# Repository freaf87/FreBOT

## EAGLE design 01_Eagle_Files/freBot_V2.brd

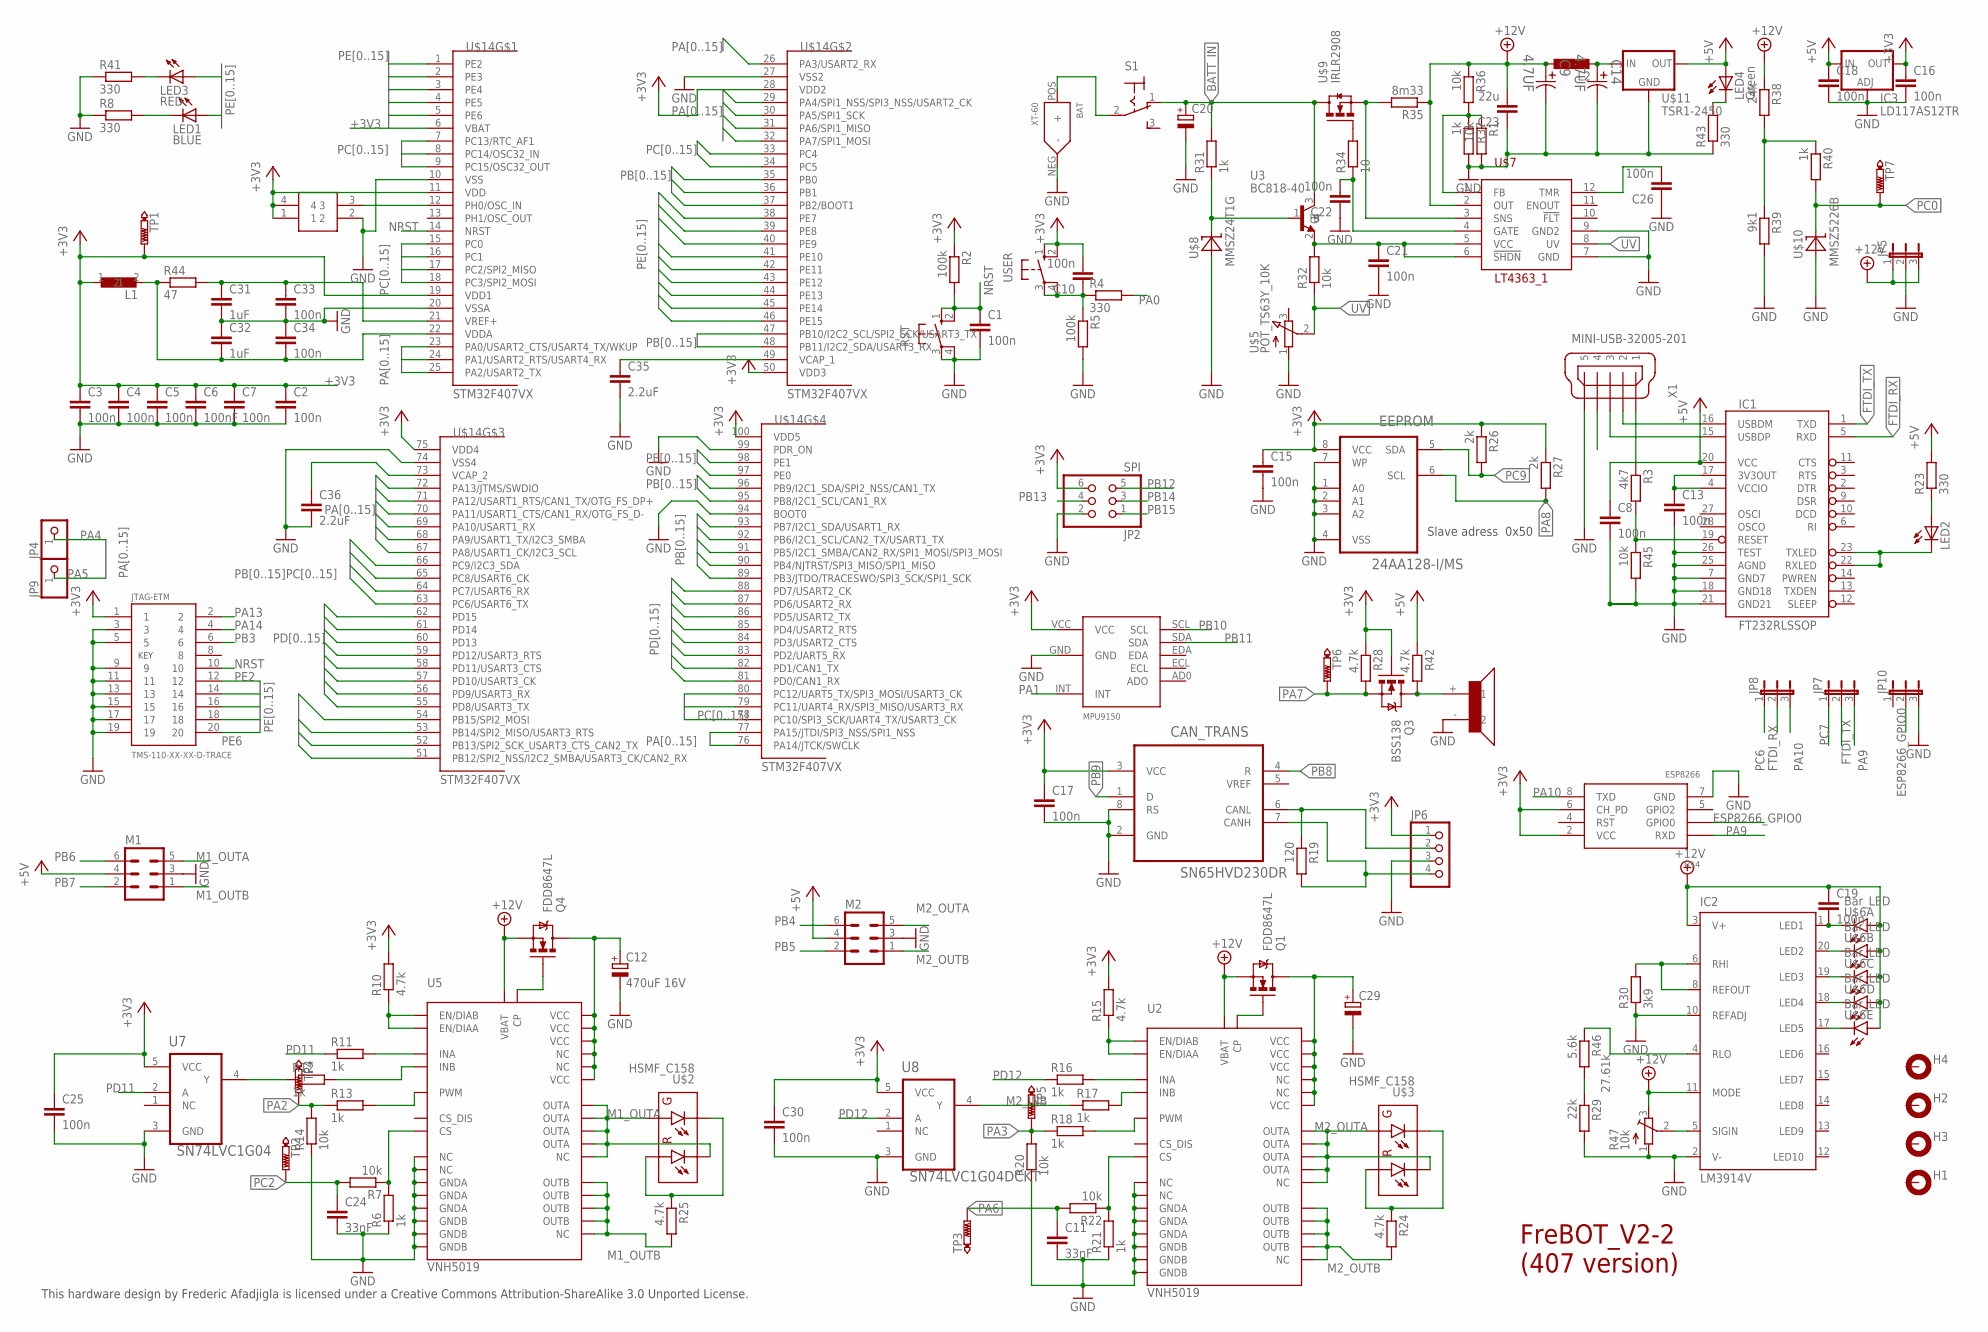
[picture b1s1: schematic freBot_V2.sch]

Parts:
BAT: XT-60
C1, C2, C3, C4, C5, C7, C8, C10, C13, C15, C16, C17, C18, C19, C21, C33, C34: 100n; C0603
C6: 100nF; C0603
C9, C14: 4.7UF; CAPAE330X560N
C11, C24: 33nF; C0805
C12: 470uF 16V; 175TMP-0808
C20: CPOL-EU153CLV-0505; 153CLV-0505
C22, C26: 100n; C0805
C23: 22u; C0805
C25, C30: 100n; C0603K
C29: CPOL-EU175TMP-0808; 175TMP-0808
C31, C32: 1uF; C0603
C35, C36: 2.2uF; C0805
CAN_TRANS: SN65HVD230DR; SOIC127P600X175-8N
EEPROM: 24AA128-I/MS; SOP65P490X110-8N
H1, H2, H3, H4: MOUNT-PAD-ROUND3.0; 3,0-PAD
IC1: FT232RLSSOP; SSOP28DB
IC2: LM3914V; PLCC20S
IC3: LD117AS12TR; SOT223
JP2: SPI; 2X03
JP4, JP9: PINHD-1X1; 1X01
JP5, JP7, JP8, JP10: JP2E; JP2
JP6: PINHD-1X4; 1X04
JTAG-ETM: TMS-110-XX-XX-D-TRACE
L1: FERRITPERLE_0805
L2: L-EUWE-TPC; POWER-CHOKE_WE-TPC
LED1: BLUE; CHIP-LED0805
LED2: LEDCHIP-LED0805; CHIP-LED0805
LED3: RED; CHIP-LED0805
LED4: Green; CHIP-LED0805
M1, M2: ML6
MPU9150: MPU9150_BREAKOUT
Q1, Q4: FDD8647L; DPAK
Q3: BSS138; SOT23-3
R1, R7, R14, R20, R22, R32, R36, R45: 10k; R0603
R2, R5: 100k; R0603
R3: 4k7; R0603
R4, R8, R23, R41, R43: 330; R0603
R6, R11, R12, R13, R16, R17, R18, R21, R31, R37, R40: 1k; R0603
R10, R15, R24, R25, R28, R42: 4.7k; R0603
R19: 120; R0603
R26, R27: 2k; R0603
R29: 22k; R0603
R30: 3k9; R0603
R34: 10; R0603
R35: 8m33; R2512
R38: 24k; R0603
R39: 9k1; R0603
R44: 47; R0603
R46: 5.6k; R0603
R47: 10k; SM-42/43A
RST: 10-XX; B3F-10XX
S1: M9040P
TP1, TP2, TP3, TP4, TP5, TP6, TP7: PTR1B1,27; B1,27
U2, U5: VNH5019
U3: BC818-40; SOT95P240X97-3N
U7: SN74LVC1G04; SOT65P210X110-5N
U8: SN74LVC1G04DCKT; SOT65P210X110-5N
U$1: CB3_OSCILLATOR
U$2, U$3: HSMF_C158
U$4: ESP8266
U$5: POT_TS63Y_10K
U$6: Bar_LED; LED_BARGRAPH_5
U$7: LT4363_1; MSOP12
U$8: MMSZ24T1G; SOD123
U$9: IRLR2908; DPAK-TO252
U$10: MMSZ5226B; SOD123
U$11: TSR1-2450
U$12: BUZZER
U$14: STM32F407VX; LQFP100
USER: 10-XX; B3F-10XX
X1: MINI-USB-32005-201; 32005-201

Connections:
+3V3: C2.1, C3.1, C4.1, C5.1, C6.1, C7.1, C10.2, C15.1, C16.1, C17.1, C25.1, C30.1, CAN_TRANS.3 (VCC), EEPROM.8 (VCC), IC3.4 (OUT), JP2.6, JP6.1, JTAG-ETM.1, L1.1, MPU9150.VCC, Q3.1 (G), R2.1, R10.2, R15.2, R26.1, R27.1, R28.1, TP1.TP, U7.5 (VCC), U8.5 (VCC), U$1.1, U$1.4, U$4.2 (VCC), U$4.6 (CH_PD), U$14.6 (VBAT), U$14.11 (VDD), U$14.19 (VDD1), U$14.28 (VDD2), U$14.50 (VDD3), U$14.75 (VDD4), U$14.100 (VDD5), USER.1 (S), USER.2 (S1)
+5V: C8.1, C18.1, IC1.20 (VCC), IC3.3 (IN), LED4.A, M1.4, M2.4, R23.2, R42.1, U$11.3 (OUT)
+12V: C9.1, C19.1, C23.2, IC2.3 (V+), IC2.11 (MODE), JP5.1, JP5.3, L2.1, Q1.3 (S), R35.1, R36.1, R38.1, R47.3 (E), U2.12 (VBAT), U5.12 (VBAT), U$6.1 (A), U$6.2 (A), U$6.3 (A), U$6.4 (A), U$6.5 (A), U$7.2 (OUT)
BATT_IN: C20.+, R31.2, S1.1 (O), U3.3 (C), U$9.4 (D)
ESP8266_GPIO0: JP10.2, U$4.3 (GPIO0)
FTDI_RX: IC1.5 (RXD), JP8.2
FTDI_TX: IC1.1 (TXD), JP7.2
GND: BAT.NEG (-), C1.2, C2.2, C3.2, C4.2, C5.2, C6.2, C7.2, C8.2, C9.2, C11.2, C12.-, C13.2, C14.2, C15.2, C16.2, C17.2, C18.2, C20.-, C21.2, C22.1, C23.1, C24.2, C25.2, C26.1, C29.-, C30.2, C31.2, C32.1, C33.2, C34.1, C35.2, C36.2, CAN_TRANS.2 (GND), CAN_TRANS.8 (RS), EEPROM.1 (A0), EEPROM.2 (A1), EEPROM.3 (A2), EEPROM.4 (VSS), EEPROM.7 (WP), IC1.7 (GND7), IC1.18 (GND18), IC1.21 (GND21), IC1.25 (AGND), IC1.26 (TEST), IC2.2 (V-), IC2.10 (REFADJ), IC3.1 (ADJ), JP2.2, JP5.2, JP6.3, JP10.3, JTAG-ETM.3, JTAG-ETM.5, JTAG-ETM.9, JTAG-ETM.11, JTAG-ETM.13, JTAG-ETM.15, JTAG-ETM.17, JTAG-ETM.19, M1.3, M2.3, MPU9150.GND, R1.2, R5.2, R6.1, R8.1, R14.1, R20.1, R21.1, R29.2, R30.1, R37.2, R39.2, R41.1, R43.1, R45.2, R47.1 (A), RST.3, RST.4 (P1), U2.17 (NC), U2.18 (GNDB), U2.19 (GNDB), U2.20 (GNDB), U2.26 (GNDA), U2.27 (GNDA), U2.28 (GNDA), U2.29 (NC), U5.17 (NC), U5.18 (GNDB), U5.19 (GNDB), U5.20 (GNDB), U5.26 (GNDA), U5.27 (GNDA), U5.28 (GNDA), U5.29 (NC), U7.3 (GND), U8.3 (GND), U$1.2, U$4.7 (GND), U$5.1 (A), U$7.7 (GND), U$7.9 (GND2), U$8.A, U$10.A, U$11.2 (GND), U$12.- (2), U$14.10 (VSS), U$14.20 (VSSA), U$14.27 (VSS2), U$14.74 (VSS4), U$14.94 (BOOT0), U$14.99 (PDR_ON), X1.5
M1_INB: R12.1, U7.4 (Y)
M1_OUTA: M1.5, U5.1 (OUTA), U5.24 (NC), U5.25 (OUTA), U5.30 (OUTA), U5.SLUG2 (OUTA), U$2.GA, U$2.RC
M1_OUTB: M1.1, R25.2, U5.15 (OUTB), U5.16 (OUTB), U5.21 (OUTB), U5.22 (NC), U5.SLUG3 (OUTB)
M2_INB: R17.1, U8.4 (Y)
M2_OUTA: M2.5, U2.1 (OUTA), U2.24 (NC), U2.25 (OUTA), U2.30 (OUTA), U2.SLUG2 (OUTA), U$3.GA, U$3.RC
M2_OUTB: M2.1, R24.2, U2.15 (OUTB), U2.16 (OUTB), U2.21 (OUTB), U2.22 (NC), U2.SLUG3 (OUTB)
unnamed: R12.2, U5.10 (INB)
unnamed: C31.1, C33.1, R44.2, U$14.21 (VREF+)
unnamed: U$1.3, U$14.12 (PH0/OSC_IN)
unnamed: IC1.19 (RESET), R3.2, R45.1
unnamed: R6.2, R7.1, U5.8 (CS)
unnamed: C29.+, Q1.4 (D), U2.2 (NC), U2.3 (VCC), U2.13 (VCC), U2.14 (NC), U2.23 (VCC), U2.SLUG1 (VCC)
unnamed: R15.1, U2.5 (EN/DIAA), U2.9 (EN/DIAB)
unnamed: R10.1, U5.5 (EN/DIAA), U5.9 (EN/DIAB)
unnamed: R11.2, U5.4 (INA)
unnamed: C12.+, Q4.4 (D), U5.2 (NC), U5.3 (VCC), U5.13 (VCC), U5.14 (NC), U5.23 (VCC), U5.SLUG1 (VCC)
unnamed: R16.2, U2.4 (INA)
unnamed: Q4.1 (G), U5.11 (CP)
unnamed: R13.2, U5.7 (PWM)
unnamed: R18.2, U2.7 (PWM)
unnamed: R17.2, U2.10 (INB)
unnamed: IC2.4 (RLO), R46.1
unnamed: CAN_TRANS.6 (CANL), JP6.2, R19.1
unnamed: R21.2, R22.1, U2.8 (CS)
unnamed: R29.1, R46.2
unnamed: C13.1, IC1.4 (VCCIO), IC1.17 (3V3OUT)
unnamed: C14.1, L2.2, U$11.1 (IN)
unnamed: Q1.1 (G), U2.11 (CP)
unnamed: LED1.C, R8.2
unnamed: IC1.22 (RXLED), IC1.23 (TXLED), LED2.C
unnamed: IC1.15 (USBDP), X1.3
unnamed: BAT.POS (+), S1.2
unnamed: LED2.A, R23.1
unnamed: R24.1, U$3.GC, U$3.RA
unnamed: Q3.3 (D), R42.2, U$12.+ (1)
unnamed: IC2.5 (SIGIN), R47.2 (S)
unnamed: C10.1, R4.1, R5.1, USER.3, USER.4 (P1)
unnamed: LED3.C, R41.2
unnamed: R25.1, U$2.GC, U$2.RA
unnamed: C19.2, IC2.1 (LED1), U$6.10 (C)
unnamed: IC2.6 (RHI), IC2.8 (REFOUT), R30.2
unnamed: IC2.20 (LED2), U$6.9 (C)
unnamed: IC2.19 (LED3), U$6.8 (C)
unnamed: IC2.18 (LED4), U$6.7 (C)
unnamed: IC2.17 (LED5), U$6.6 (C)
unnamed: R31.1, U3.1 (B), U$8.C
unnamed: R34.2, U$9.1 (G)
unnamed: C21.1, R32.2, U3.2 (E), U$7.5 (VCC), U$7.6 (!SHDN)
unnamed: C22.2, R34.1, U$7.4 (GATE)
unnamed: R35.2, U$7.3 (SNS), U$9.3 (S)
unnamed: C26.2, U$7.12 (TMR)
unnamed: R1.1, R36.2, R37.1, U$7.1 (FB)
unnamed: C32.2, C34.2, L1.2, R44.1, U$14.22 (VDDA)
unnamed: R38.2, R39.1, R40.1
unnamed: LED4.C, R43.2
unnamed: C35.1, U$14.49 (VCAP_1)
unnamed: CAN_TRANS.7 (CANH), JP6.4, R19.2
unnamed: IC1.16 (USBDM), X1.2
unnamed: C36.1, U$14.73 (VCAP_2)
NRST: C1.1, JTAG-ETM.10, R2.2, RST.1 (S), RST.2 (S1), U$14.14 (NRST)
PA0: R4.2, U$14.23 (PA0/USART2_CTS/USART4_TX/WKUP)
PA1: MPU9150.INT, U$14.24 (PA1/USART2_RTS/USART4_RX)
PA2: R13.1, R14.2, TP4.TP, U$14.25 (PA2/USART2_TX)
PA3: R18.1, R20.2, TP5.TP, U$14.26 (PA3/USART2_RX)
PA4: JP4.1, U$14.29 (PA4/SPI1_NSS/SPI3_NSS/USART2_CK)
PA5: JP9.1, U$14.30 (PA5/SPI1_SCK)
PA6: C11.1, R22.2, TP3.TP, U$14.31 (PA6/SPI1_MISO)
PA7: Q3.2 (S), R28.2, TP6.TP, U$14.32 (PA7/SPI1_MOSI)
PA8: EEPROM.6 (SCL), R27.2, U$14.67 (PA8/USART1_CK/I2C3_SCL)
PA9: JP7.3, U$4.1 (RXD), U$14.68 (PA9/USART1_TX/I2C3_SMBA)
PA10: JP8.3, U$4.8 (TXD), U$14.69 (PA10/USART1_RX)
PA11: U$14.70 (PA11/USART1_CTS/CAN1_RX/OTG_FS_D-)
PA12: U$14.71 (PA12/USART1_RTS/CAN1_TX/OTG_FS_DP+)
PA13: JTAG-ETM.2, U$14.72 (PA13/JTMS/SWDIO)
PA14: JTAG-ETM.4, U$14.76 (PA14/JTCK/SWCLK)
PA15: U$14.77 (PA15/JTDI/SPI3_NSS/SPI1_NSS)
PB0: U$14.35 (PB0)
PB1: U$14.36 (PB1)
PB2: U$14.37 (PB2/BOOT1)
PB3: JTAG-ETM.6, U$14.89 (PB3/JTDO/TRACESWO/SPI3_SCK/SPI1_SCK)
PB4: M2.6, U$14.90 (PB4/NJTRST/SPI3_MISO/SPI1_MISO)
PB5: M2.2, U$14.91 (PB5/I2C1_SMBA/CAN2_RX/SPI1_MOSI/SPI3_MO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)
PB6: M1.6, U$14.92 (PB6/I2C1_SCL/CAN2_TX/USART1_TX)
PB7: M1.2, U$14.93 (PB7/I2C1_SDA/USART1_RX)
PB8: CAN_TRANS.4 (R), U$14.95 (PB8/I2C1_SCL/CAN1_RX)
PB9: CAN_TRANS.1 (D), U$14.96 (PB9/I2C1_SDA/SPI2_NSS/CAN1_TX)
PB10: MPU9150.SCL, U$14.47 (PB10/I2C2_SCL/SPI2_SCK/USART3_TX)
PB11: MPU9150.SDA, U$14.48 (PB11/I2C2_SDA/USART3_RX)
PB12: JP2.5, U$14.51 (PB12/SPI2_NSS/I2C2_SMBA/USART3_CK/CAN2_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)
PB13: JP2.4, U$14.52 (PB13/SPI2_SCK_USART3_CTS_CAN2_TX)
PB14: JP2.3, U$14.53 (PB14/SPI2_MISO/USART3_RTS)
PB15: JP2.1, U$14.54 (PB15/SPI2_MOSI)
PC0: R40.2, TP7.TP, U$10.C, U$14.15 (PC0)
PC1: U$14.16 (PC1)
PC2: C24.1, R7.2, TP2.TP, U$14.17 (PC2/SPI2_MISO)
PC3: U$14.18 (PC3/SPI2_MOSI)
PC4: U$14.33 (PC4)
PC5: U$14.34 (PC5)
PC6: JP8.1, U$14.63 (PC6/USART6_TX)
PC7: JP7.1, U$14.64 (PC7/USART6_RX)
PC8: U$14.65 (PC8/USART6_CK)
PC9: EEPROM.5 (SDA), R26.2, U$14.66 (PC9/I2C3_SDA)
PC10: U$14.78 (PC10/SPI3_SCK/UART4_TX/USART3_CK)
PC11: U$14.79 (PC11/UART4_RX/SPI3_MISO/USART3_RX)
PC12: U$14.80 (PC12/UART5_TX/SPI3_MOSI/USART3_CK)
PC13: U$14.7 (PC13/RTC_AF1)
PC14: U$14.8 (PC14/OSC32_IN)
PC15: U$14.9 (PC15/OSC32_OUT)
PD0: U$14.81 (PD0/CAN1_RX)
PD1: U$14.82 (PD1/CAN1_TX)
PD2: U$14.83 (PD2/UART5_RX)
PD3: U$14.84 (PD3/USART2_CTS)
PD4: U$14.85 (PD4/USART2_RTS)
PD5: U$14.86 (PD5/USART2_TX)
PD6: U$14.87 (PD6/USART2_RX)
PD7: U$14.88 (PD7/USART2_CK)
PD8: U$14.55 (PD8/USART3_TX)
PD9: U$14.56 (PD9/USART3_RX)
PD10: U$14.57 (PD10/USART3_CK)
PD11: R11.1, U7.2 (A), U$14.58 (PD11/USART3_CTS)
PD12: R16.1, U8.2 (A), U$14.59 (PD12/USART3_RTS)
PD13: U$14.60 (PD13)
PD14: U$14.61 (PD14)
PD15: U$14.62 (PD15)
PE0: LED3.A, U$14.97 (PE0)
PE1: LED1.A, U$14.98 (PE1)
PE2: JTAG-ETM.12, U$14.1 (PE2)
PE3: JTAG-ETM.14, U$14.2 (PE3)
PE4: JTAG-ETM.16, U$14.3 (PE4)
PE5: JTAG-ETM.18, U$14.4 (PE5)
PE6: JTAG-ETM.20, U$14.5 (PE6)
PE7: U$14.38 (PE7)
PE8: U$14.39 (PE8)
PE9: U$14.40 (PE9)
PE10: U$14.41 (PE10)
PE11: U$14.42 (PE11)
PE12: U$14.43 (PE12)
PE13: U$14.44 (PE13)
PE14: U$14.45 (PE14)
PE15: U$14.46 (PE15)
USB_5V: R3.1, X1.1
UV: R32.1, U$5.2 (S), U$7.8 (UV)

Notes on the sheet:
This hardware design by Frederic Afadjigla is licensed under a Creative Commons Attribution-ShareAlike 3.0 Unported License.
Slave adress 0x50
FreBOT_V2-2 (407 version)
27.61k

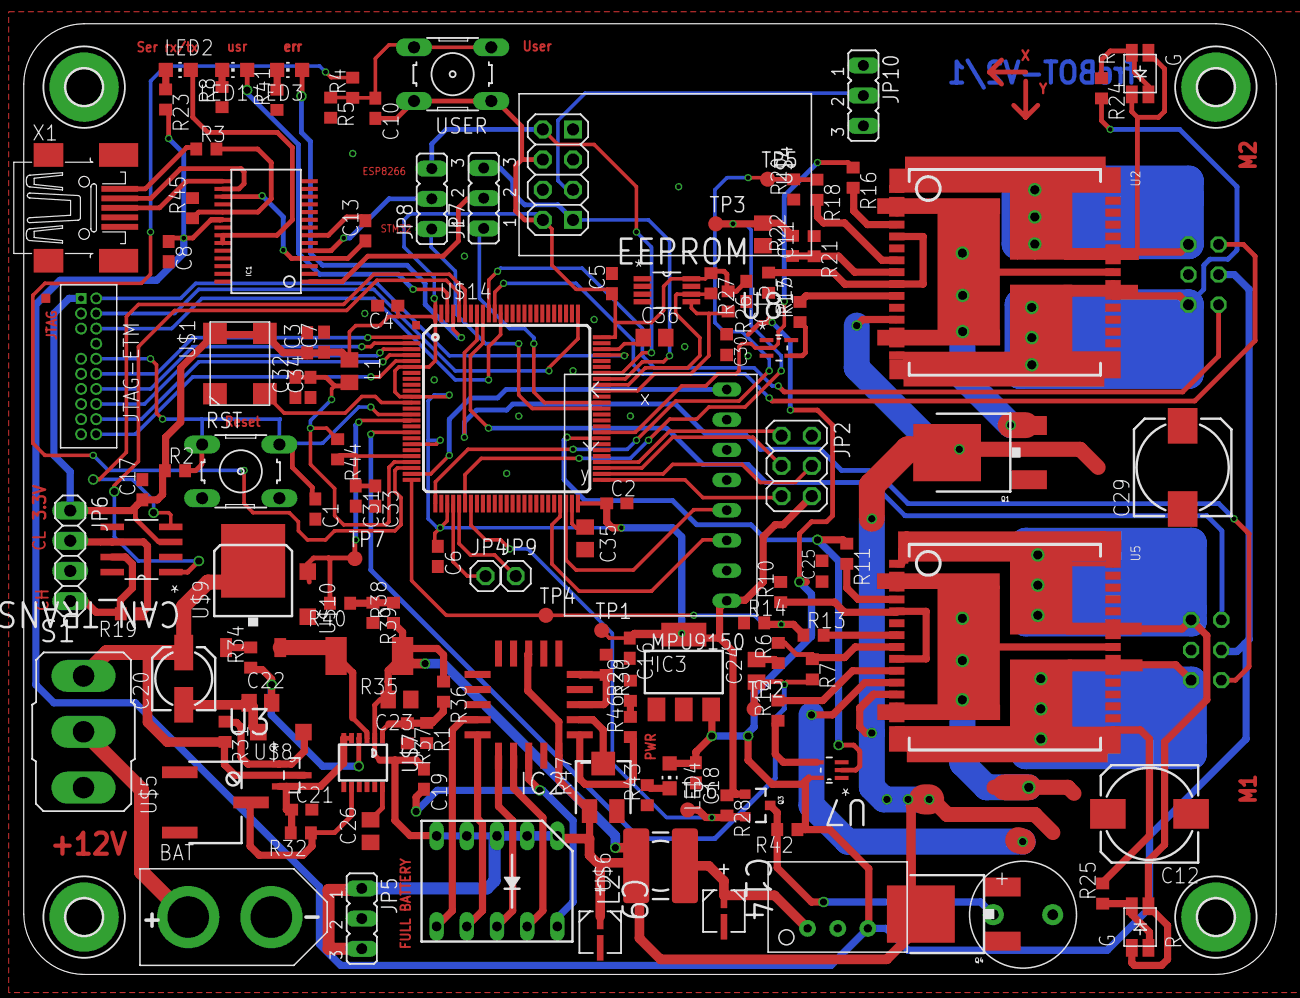
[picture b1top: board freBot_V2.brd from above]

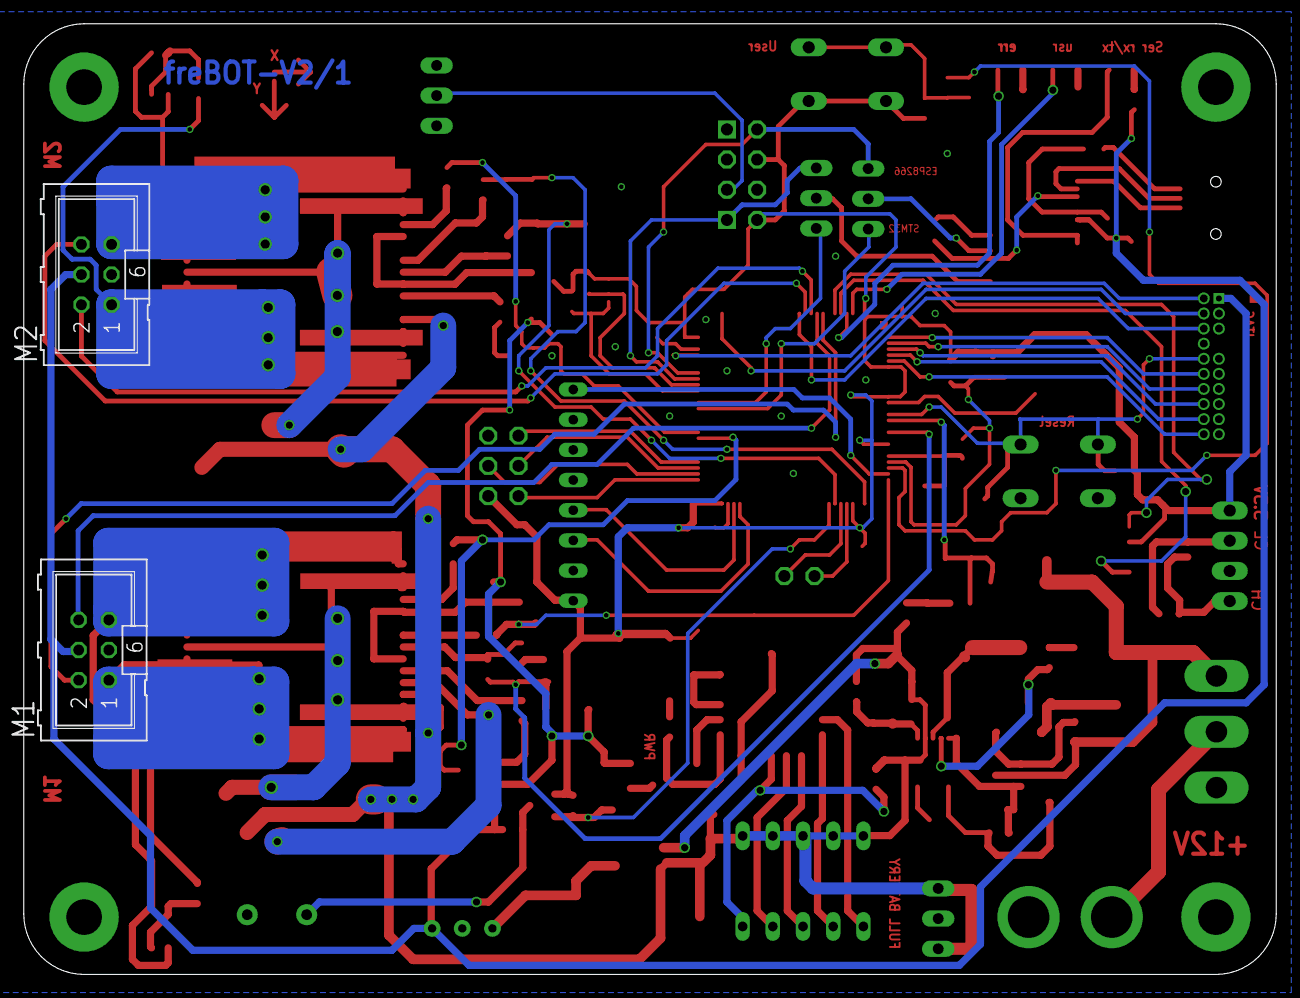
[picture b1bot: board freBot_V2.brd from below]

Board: 2 copper layers, 105.4 x 80.0 mm, 139 parts (2 on the bottom side), 110 nets.

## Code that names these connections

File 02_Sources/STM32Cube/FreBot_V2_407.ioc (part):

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Mcu.Name=STM32F407V(E-G)Tx
Mcu.Package=LQFP100
Mcu.UserName=STM32F407VGTx
PA1.Signal=GPIO_Input
PA10.Mode=Asynchronous
PA10.Signal=USART1_RX
PA11.Mode=CTS_RTS
PA11.Signal=USART1_CTS
PA12.Mode=CTS_RTS
PA12.Signal=USART1_RTS
PA13.Mode=Trace-Synchro(4bits)_JTAG
PA13.Signal=SYS_JTMS-SWDIO
PA14.Mode=Trace-Synchro(4bits)_JTAG
PA14.Signal=SYS_JTCK-SWCLK
PA15.Mode=Trace-Synchro(4bits)_JTAG
PA15.Signal=SYS_JTDI
PA2.Signal=S_TIM9_CH1
PA3.Signal=S_TIM9_CH2
PA4.Signal=COMP_DAC1_group
PA5.Signal=COMP_DAC2_group
PA6.Signal=ADCx_IN6
PA7.Signal=S_TIM14_CH1
PA8.Mode=I2C
PA8.Signal=I2C3_SCL
PA9.Mode=Asynchronous
PA9.Signal=USART1_TX
PB10.Mode=I2C
PB10.Signal=I2C2_SCL
PB11.Mode=I2C
PB11.Signal=I2C2_SDA
PB12.Mode=NSS_Signal_Hard
PB12.Signal=SPI2_NSS
PB13.Mode=Full_Duplex_Master
PB13.Signal=SPI2_SCK
PB14.Mode=Full_Duplex_Master
PB14.Signal=SPI2_MISO
PB15.Mode=Full_Duplex_Master
PB15.Signal=SPI2_MOSI
PB3.Mode=Trace-Synchro(4bits)_JTAG
PB3.Signal=SYS_JTDO-SWO
PB4.Signal=S_TIM3_CH1
PB5.Signal=S_TIM3_CH2
PB6.Signal=S_TIM4_CH1
PB7.Signal=S_TIM4_CH2
PB8.Mode=Master
PB8.Signal=CAN1_RX
PB9.Mode=Master
PB9.Signal=CAN1_TX
PC0.Signal=ADCx_IN10
PC2.Signal=ADCx_IN12
PC6.Mode=Asynchronous
PC6.Signal=USART6_TX
PC7.Mode=Asynchronous
PC7.Signal=USART6_RX
PC9.Mode=I2C
PC9.Signal=I2C3_SDA
PD11.GPIOParameters=GPIO_Label
PD11.GPIO_Label=M1_IN
PD11.Signal=GPIO_Output
PD12.GPIOParameters=GPIO_Label
PD12.GPIO_Label=M2_IN
PD12.Signal=GPIO_Output
PE0.GPIOParameters=GPIO_Label
PE0.GPIO_Label=ERR_LED
PE0.Signal=GPIO_Output
PE1.GPIOParameters=GPIO_Label
PE1.GPIO_Label=USR_LED
PE1.Signal=GPIO_Output
PE2.Mode=Trace-Synchro(4bits)_JTAG
PE2.Signal=SYS_TRACECLK
PE3.Mode=Trace-Synchro(4bits)_JTAG
PE3.Signal=SYS_TRACED0
PE4.Mode=Trace-Synchro(4bits)_JTAG
PE4.Signal=SYS_TRACED1
PE5.Mode=Trace-Synchro(4bits)_JTAG
PE5.Signal=SYS_TRACED2
PE6.Mode=Trace-Synchro(4bits)_JTAG
PE6.Signal=SYS_TRACED3
RCC.HSE_VALUE=25000000
RCC.SYSCLKFreq_VALUE=16000000
board=custom

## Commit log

2015-12-12 mpu9150 files added
2015-12-12 mpu9150 Lib added
2015-12-19 Code restructuring & motor component added
2015-12-19 Code restructuring

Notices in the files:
parts and their libraries:
SparkFun: Licensing: CC v3.0 Share-Alike You are welcome to use this library for commercial purposes.
SparkFun-DiscreteSemi: Licensing: Creative Commons ShareAlike 4.0 International - https://creativecommons.org/licenses/by-sa/4.0
